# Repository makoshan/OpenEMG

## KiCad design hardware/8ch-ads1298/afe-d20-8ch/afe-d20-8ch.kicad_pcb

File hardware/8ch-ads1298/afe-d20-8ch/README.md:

# C08B 纯单面 8 通道采集板 · 圆孔版 D20-8CH（2026-11-12）

基于 C08B 正面基准布局 人工正面布局与已修清全部安全/电气缺陷的 `../../16ch-c08b-round/afe-d20/afe-d20-silk.kicad_pcb`（`31323826…`）派生，同步吸收 `ProPrj_ads1298v3.4` 单颗 ADS1298 八路拓扑：

- **纯正面单面贴**：保留正面全部 76 颗贴片器件（`V4_U1` ADS1298 CH1–8、`V4_FPC1` 34P、`J_AFE` 20P、`V4_LM27762` ±2.5V、`V4_X1` 2.048 MHz、`D910–D927` ESD401、`V4_U3–U6` 15k 排阻、`V4_C72–C79` 22 pF 差分电容、`V4_R18` 0R 单点接地、`V4_R34` 392 kΩ RLD 限流）+ `TP901/TP902` + `H901–H904`；删除背面全部 53 个封装（51 颗贴片 + `TP903/TP904`）。
- **背面整面绿油绝缘**：`B.Paste = 0`、`B.Mask = 0`，背面无裸露焊盘或凸起阻容，可直接贴合 `302025` 锂电池；省去双面贴片换面费。
- **主控与外壳 1:1 兼容**：板框 `43.10 × 36.50 mm` 与 `D20` 完全一致，`J_AFE`（20P）与主控板 `R4U6` 逐脚对插（3/4 脚 `ADS_DRDY_B`/`ADS_CS_B` 置为 `NC`）。
- **走线与 DRC**：仅对原借道背面焊盘连通正面的 7 条网络补齐纳米级 135°/共线桥接，剪除 140 段残桩与 10 颗单端过孔，倒角 `V4_REF2` 原三岔口留下的 1 处 90° 拐角。KiCad 10 DRC（含重铺）0 违规 / 0 未连，`route_lint` 七项硬指标全 0，`smt_dfm_gate` 通过。

## 图纸、逐针核对表与嘉立创工程（对标 16 通道 v0.01 交付标准）

| 文件 / 目录 | 说明 |
|---|---|
| [`PINOUT-AND-REVIEW.md`](PINOUT-AND-REVIEW.md) · [`pinout-34p-20p.csv`](pinout-34p-20p.csv) | **34P 表带接口（`V4_FPC1`）与 20P 板间接口（`J_AFE` `k ↔ 21−k`）逐针核对总表**、固件寄存器表、制造包 SHA-256 绑定与五阶段验收记录表 |
| [`views/schematic.pdf`](views/schematic.pdf) | **11 页全套矢量可搜索原理图 PDF**（P1 整机框图、P2 电源树、P3–P7 主控板 `R4U6`、P8–P11 采集板 `D20-8CH`） |
| [`views/afe-schematic.pdf`](views/afe-schematic.pdf) | **6 页采集板独立矢量可搜索原理图 PDF**（P1 整机框图、P2 电源树、P3–P6 采集板详图；同步更新 [`schematics-8ch/C08B-8ch采集板原理图-D20-8CH-20261113.pdf`](schematics-8ch/C08B-8ch采集板原理图-D20-8CH-20261113.pdf)） |
| [`views/d20-8ch-wiring-orientation.svg`](views/d20-8ch-wiring-orientation.svg) · [`.png`](views/d20-8ch-wiring-orientation.png) | **贴肤侧 18 枚电极编号（盒底 6 + 北短带 4 + 南长带 8）与 34P/20P 座子开口朝向核对图** |
| [`views/d20-8ch-system-zh.svg`](views/d20-8ch-system-zh.svg) · [`-en.svg`](views/d20-8ch-system-en.svg) | P1 整机框图（中英双语矢量图） |
| [`views/d20-8ch-power-zh.svg`](views/d20-8ch-power-zh.svg) · [`-en.svg`](views/d20-8ch-power-en.svg) | P2 电源树与实测记录栏（中英双语矢量图） |
| [`views/afe-copper.png`](views/afe-copper.png) · [`views/schematic-afe-input-preview.png`](views/schematic-afe-input-preview.png) | 4 层铜皮预览与 34P 电极输入保护页预览 |
| [`jlc-eda/C08B-8ch全套汇总-主控R4U6-采集D20-8CH单面.epro2`](jlc-eda/C08B-8ch全套汇总-主控R4U6-采集D20-8CH单面.epro2) | 嘉立创 EDA 专业版全套双板工程（含 **11 页原理图**：`01.01 整机框图`、`01.02 电源树`、主控 5 页、采集 4 页） |
| [`jlc-eda/C08B-AFE采集板-D20-8CH-单面8路-原理图+PCB+3D.epro2`](jlc-eda/C08B-AFE采集板-D20-8CH-单面8路-原理图+PCB+3D.epro2) | 嘉立创 EDA 专业版采集板独立工程（含 **6 页原理图**：`01.01 整机框图`、`01.02 电源树`、采集 4 页） |

状态：**待人工工程师独立审板**（自动化逐脚对板与 DRC 已过；未人工审板、未打样、未上台架、未过人体安全门）。

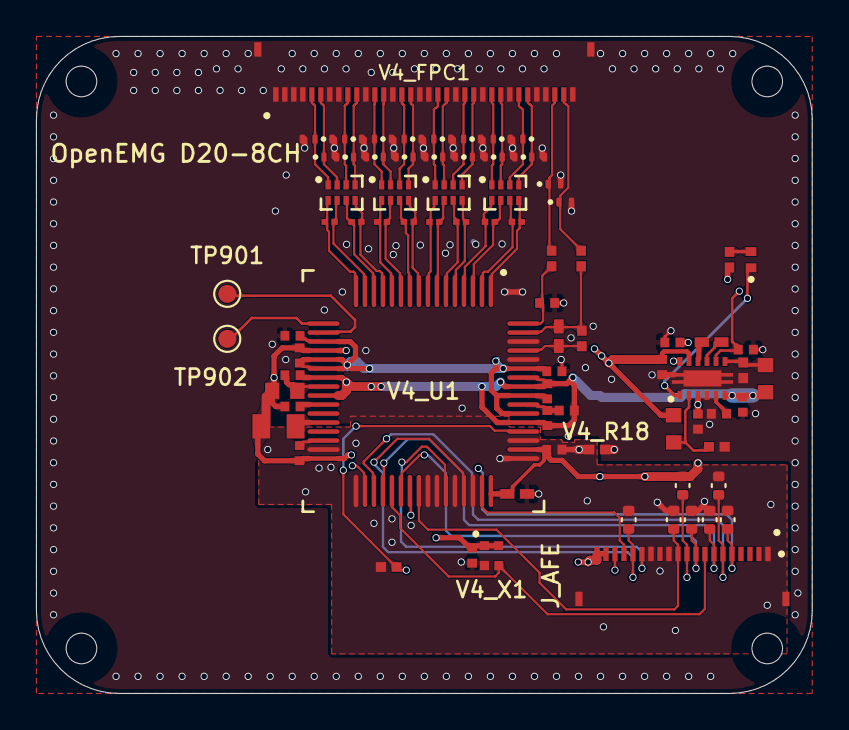
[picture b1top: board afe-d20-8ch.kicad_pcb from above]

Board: 4 copper layers, 43.1 x 36.5 mm, 82 parts (0 on the bottom side), 67 nets.

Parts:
C901: 10uF; C901
C902: 4.7uF; C902
D901: XL-1005UGC; D901
D910: ESD401DPYR; D910
D911: ESD401DPYR; D911
D912: ESD401DPYR; D912
D913: ESD401DPYR; D913
D914: ESD401DPYR; D914
D915: ESD401DPYR; D915
D916: ESD401DPYR; D916
D917: ESD401DPYR; D917
D918: ESD401DPYR; D918
D919: ESD401DPYR; D919
D920: ESD401DPYR; D920
D921: ESD401DPYR; D921
D922: ESD401DPYR; D922
D923: ESD401DPYR; D923
D924: ESD401DPYR; D924
D925: ESD401DPYR; D925
D926: ESD401DPYR; D926
D927: ESD401DPYR; D927
H901: M1.4 NPTH 1.7; H901
H902: M1.4 NPTH 1.7; H902
H903: M1.4 NPTH 1.7; H903
H904: M1.4 NPTH 1.7; H904
J_AFE: FH34SRJ-20S-0.5SH(50) (LCSC C2802370); Hirose_FH34SRJ-20S-0.5SH
R801: 10k; R801
R803: 10k; R803
R804: 10k; R804
R805: 10k; R805
R806: 10k; R806
R807: 10k; R807
R808: 10k; R808
R901: 10kΩ; R901
TP901: V4_REF2; TP901
TP902: V4_REF1; TP902
V4_C31: 1uF; V4_C31
V4_C32: 100nF; V4_C32
V4_C33: 1uF; V4_C33
V4_C34: 100nF; V4_C34
V4_C35: 1uF; V4_C35
V4_C36: 100nF; V4_C36
V4_C37: 100nF; V4_C37
V4_C43: 1uF; V4_C43
V4_C44: 1uF; V4_C44
V4_C45: 100nF; V4_C45
V4_C46: 10uF; V4_C46
V4_C47: 10nF; V4_C47
V4_C48: 100nF; V4_C48
V4_C49: 1uF; V4_C49
V4_C50: 100nF; V4_C50
V4_C54: 22uF; V4_C54
V4_C72: 22pF; V4_C72
V4_C73: 22pF; V4_C73
V4_C74: 22pF; V4_C74
V4_C75: 22pF; V4_C75
V4_C76: 22pF; V4_C76
V4_C77: 22pF; V4_C77
V4_C78: 22pF; V4_C78
V4_C79: 22pF; V4_C79
V4_C81: 100nF; V4_C81
V4_C82: 100nF; V4_C82
V4_C83: 2.2uF; V4_C83
V4_C84: 2.2uF; V4_C84
V4_C123: 100pF; V4_C123
V4_FPC1: FH34SRJ-34S-0.5SH(50) (LCSC C424660); Hirose_FH34SRJ-34S-0.5SH
V4_LM27762: LM27762DSSR; V4_LM27762
V4_R17: 10K; V4_R17
V4_R18: 0R; V4_R18
V4_R24: 392K; V4_R24
V4_R26: 107k; V4_R26
V4_R27: 100kΩ; V4_R27
V4_R28: 100kΩ; V4_R28
V4_R29: 104k; V4_R29
V4_R34: 392K; V4_R34
V4_R35: 10K; V4_R35
V4_U1: ADS1298IPAGR; V4_U1
V4_U3: 15kΩ; V4_U3
V4_U4: 15kΩ; V4_U4
V4_U5: 15kΩ; V4_U5
V4_U6: 15kΩ; V4_U6
V4_X1: 2.048MHz; V4_X1

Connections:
3V3: C901.2, J_AFE.19, J_AFE.20, R801.2, R901.1, V4_C31.2, V4_C32.2, V4_C37.2, V4_C81.2, V4_C82.2, V4_LM27762.3, V4_LM27762.8, V4_LM27762.12, V4_U1.48, V4_U1.50, V4_X1.1, V4_X1.4
ADS_CLKSEL: J_AFE.18, V4_R17.2, V4_U1.52
ADS_CS_A: J_AFE.10, R801.1, V4_U1.39
ADS_DRDY_A: J_AFE.17, V4_U1.47
ADS_PWDN: J_AFE.6, R804.1, V4_U1.35
ADS_RESET: J_AFE.7, R803.1, V4_U1.36
ADS_START: J_AFE.9, R805.1, V4_U1.38
AFE_CLK_IN: J_AFE.8, V4_U1.37, V4_X1.3
AFE_GPIO3: J_AFE.16, R808.1, V4_U1.45
AGND: C901.1, C902.1, D910.2, D911.2, D912.2, D913.2, D914.2, D915.2, D916.2, D917.2, D918.2, D919.2, D920.2, D921.2, D922.2, D923.2, D924.2, D925.2, D926.2, D927.2, V4_C33.1, V4_C34.1, V4_C81.1, V4_C82.1, V4_C83.1, V4_C84.1, V4_C123.2, V4_FPC1.1, V4_FPC1.2, V4_FPC1.3, V4_FPC1.4, V4_FPC1.7, V4_FPC1.8, V4_FPC1.11, V4_FPC1.14, V4_FPC1.17, V4_FPC1.18, V4_FPC1.21, V4_FPC1.24, V4_FPC1.27, V4_FPC1.30, V4_FPC1.31, V4_FPC1.34, V4_FPC1.MP, V4_LM27762.4, V4_LM27762.13, V4_R18.2, V4_R27.1, V4_R28.2, V4_U1.60, V4_U1.62
DIN_B: J_AFE.5, R807.1, V4_U1.34
DOUT_B: J_AFE.15, V4_U1.43
GND: J_AFE.1, J_AFE.12, J_AFE.14, J_AFE.21, J_AFE.22, R803.2, R804.2, R805.2, R806.2, R807.2, R808.2, V4_C31.1, V4_C32.1, V4_C37.1, V4_R17.1, V4_R18.1, V4_U1.31, V4_U1.33, V4_U1.41, V4_U1.42, V4_U1.44, V4_U1.46, V4_U1.49, V4_U1.51, V4_X1.2
SCLK_B: J_AFE.11, R806.1, V4_U1.40
V4_$1N19: V4_C45.2, V4_C46.1, V4_U1.24
V4_$1N24: V4_C44.2, V4_U1.26
V4_$1N25: V4_C54.2, V4_U1.28
V4_$1N26: V4_C43.2, V4_U1.30
V4_$1N44: V4_C48.2, V4_C49.1, V4_U1.55
V4_$1N350: V4_C123.1, V4_R35.1, V4_U1.64
V4_$2N83: D927.1, V4_FPC1.5, V4_U6.1
V4_$2N85: D926.1, V4_FPC1.6, V4_U6.2
V4_$2N86: D925.1, V4_FPC1.9, V4_U6.3
V4_$2N87: D924.1, V4_FPC1.10, V4_U6.4
V4_$2N90: D921.1, V4_FPC1.15, V4_U5.3
V4_$2N93: D918.1, V4_FPC1.20, V4_U4.2
V4_$2N94: D917.1, V4_FPC1.22, V4_U4.3
V4_$2N95: D916.1, V4_FPC1.23, V4_U4.4
V4_$2N96: D915.1, V4_FPC1.25, V4_U3.1
V4_$2N97: D914.1, V4_FPC1.26, V4_U3.2
V4_$2N98: D913.1, V4_FPC1.28, V4_U3.3
V4_$2N111: D919.1, V4_FPC1.19, V4_U4.1
V4_$2N118: D923.1, V4_FPC1.12, V4_U5.1
V4_$2N119: D922.1, V4_FPC1.13, V4_U5.2
V4_$2N120: D920.1, V4_FPC1.16, V4_U5.4
V4_$2N121: D912.1, V4_FPC1.29, V4_U3.4
V4_$3N49: D901.2, R901.2
V4_$3N56: V4_LM27762.2, V4_R26.1, V4_R27.2
V4_$3N57: V4_C50.1, V4_LM27762.9
V4_$3N58: V4_C50.2, V4_LM27762.10
V4_$3N60: V4_LM27762.7, V4_R28.1, V4_R29.2
V4_$3N62: C902.2, V4_LM27762.5
V4_+2.5V: V4_C33.2, V4_C34.2, V4_C35.2, V4_C36.2, V4_C83.2, V4_LM27762.11, V4_R26.2, V4_U1.19, V4_U1.21, V4_U1.22, V4_U1.54, V4_U1.56, V4_U1.59
V4_-2.5V: V4_C35.1, V4_C36.1, V4_C43.1, V4_C44.1, V4_C45.1, V4_C46.2, V4_C48.1, V4_C49.2, V4_C54.1, V4_C84.2, V4_LM27762.6, V4_R29.1, V4_U1.20, V4_U1.23, V4_U1.25, V4_U1.32, V4_U1.53, V4_U1.57, V4_U1.58
V4_BIASINV1: V4_C47.1, V4_R24.1, V4_U1.61
V4_BIASOUT1: V4_C47.2, V4_R24.2, V4_R34.1, V4_U1.63
V4_BIAS_DRV1: D910.1, V4_FPC1.33, V4_R34.2
V4_IN1N: V4_C72.1, V4_U1.15, V4_U6.7
V4_IN1P: V4_C72.2, V4_U1.16, V4_U6.8
V4_IN2N: V4_C73.1, V4_U1.13, V4_U6.5
V4_IN2P: V4_C73.2, V4_U1.14, V4_U6.6
V4_IN3N: V4_C74.1, V4_U1.11, V4_U5.7
V4_IN3P: V4_C74.2, V4_U1.12, V4_U5.8
V4_IN4N: V4_C75.1, V4_U1.9, V4_U5.5
V4_IN4P: V4_C75.2, V4_U1.10, V4_U5.6
V4_IN5N: V4_C76.1, V4_U1.7, V4_U4.7
V4_IN5P: V4_C76.2, V4_U1.8, V4_U4.8
V4_IN6N: V4_C77.1, V4_U1.5, V4_U4.5
V4_IN6P: V4_C77.2, V4_U1.6, V4_U4.6
V4_IN7N: V4_C78.1, V4_U1.3, V4_U3.7
V4_IN7P: V4_C78.2, V4_U1.4, V4_U3.8
V4_IN8N: V4_C79.1, V4_U1.1, V4_U3.5
V4_IN8P: V4_C79.2, V4_U1.2, V4_U3.6
V4_POWERGOOD: D901.1, V4_LM27762.1
V4_REF1: TP902.1, V4_U1.17
V4_REF2: TP901.1, V4_U1.18
V4_WCT: D911.1, V4_FPC1.32, V4_R35.2

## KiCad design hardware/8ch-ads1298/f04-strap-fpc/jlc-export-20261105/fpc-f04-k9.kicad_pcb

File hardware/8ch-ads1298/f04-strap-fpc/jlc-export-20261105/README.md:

# F04 八通道软板导入嘉立创EDA（2026-11-05）

状态：已实现未验收。交付文件 `exports/嘉立创-F04-八通道软板-20261105/F04-八通道软板-原理图+PCB.epro2`，含原理图和 PCB。下单仍以 `v12/strap-f04-order/F04-FPC-样品打样5片.zip` 为准；软板源文件和订单未改。

## 重出步骤

官方 CLI 要在 Bash 沙箱外跑（沙箱里 `open` 不返回）。全程用无头会话，不碰别的窗口。

1. `python3 tools/kicad10_to_9_nets.py ../fpc-f04.kicad_pcb fpc-f04-k9.kicad_pcb`：KiCad 10 写法导入会丢铜线。
2. `python3 k9_no_tail_paste.py fpc-f04-k9.kicad_pcb`：尾端 17 个手焊盘本来没有 F.Paste，嘉立创导入后会自动开钢网，这里加负余量关掉。
3. K9 板连同 `.kicad_pro`、`.kicad_sch`、`FPC.kicad_sym`、两个 lib-table、`FPC.pretty/` 压成 zip，板文件名用 `fpc-f04.kicad_pcb`。
4. easyeda-eprj3 的 `init.js` 建空工程，`python3 import_f04.py <工程.eprj3> <zip>` 导入并配板。
5. `../../c08-eprj3-20261102/sync_uid.py <工程文件夹>` 配对元件编号，`python3 apply_rules_f04.py <工程.eprj3>` 写规则（铜间距 0.10、线宽 ≥ 0.15、铜到板边 0.30）。
6. `../../c08-eprj3-20261102/export_epro2.py <工程.eprj3> <输出.epro2>`。

## 验证（量导出的文件，不只量源工程）

| 项 | 结果 | 证据 |
|---|---|---|
| 器件 / 走线 / 飞线 | 18 = 18，799 = 799，飞线 0 | `verify-source.json`、`reimport-check.json` |
| 焊盘网络 | 34 个逻辑脚 0 不符；17 网长度差 0 | `verify-source.json` |
| 嘉立创解析的原理图网表对 PCB | 34 脚 0 不符 | `native-check.json` |
| 导回后 DRC | 只剩 Netlist Error 1 条 | `reimport-check.json` |
| DRC 阳性对照 | 注入异网短线报 2 条线距、1 条焊盘距、2 条连接错误，删除后恢复 | `reimport-check.json` |
| 铜 / 覆盖膜开窗 / 钢网 Gerber 对下单包 | 异或面积 0.0006 / 0 / 0 mm² | `gerber-diff.json` |
| Gerber 比对阳性对照 | 修钢网前报差异 30.6 mm²，正好是 17 × 3.0 × 0.6 | 本轮输出 |

## 已知差异

- **Netlist Error 1 条**：原理图和 PCB 的器件属性不同（`Name`、`Channel ID`、引脚名等），网络一致。改 PCB 的 `Name` 后这条仍在，没再追。
- **丝印字更小**：26 个字内容和中心位置都对，嘉立创字体比 KiCad 小约四成。
- **板框线宽**：中心线都是 186.8×23 mm；嘉立创线宽 0.15，下单包 0.05。
- **未比对**：PI 补强只作为自定义层上的矩形框导入。叠层没写成 106 µm 软板，在嘉立创里一键下单不能代替 `FAB-SPEC.md`。

`fpc-f04-k9.kicad_pcb` 是中间板，不入库，也不要拿回 KiCad 改。

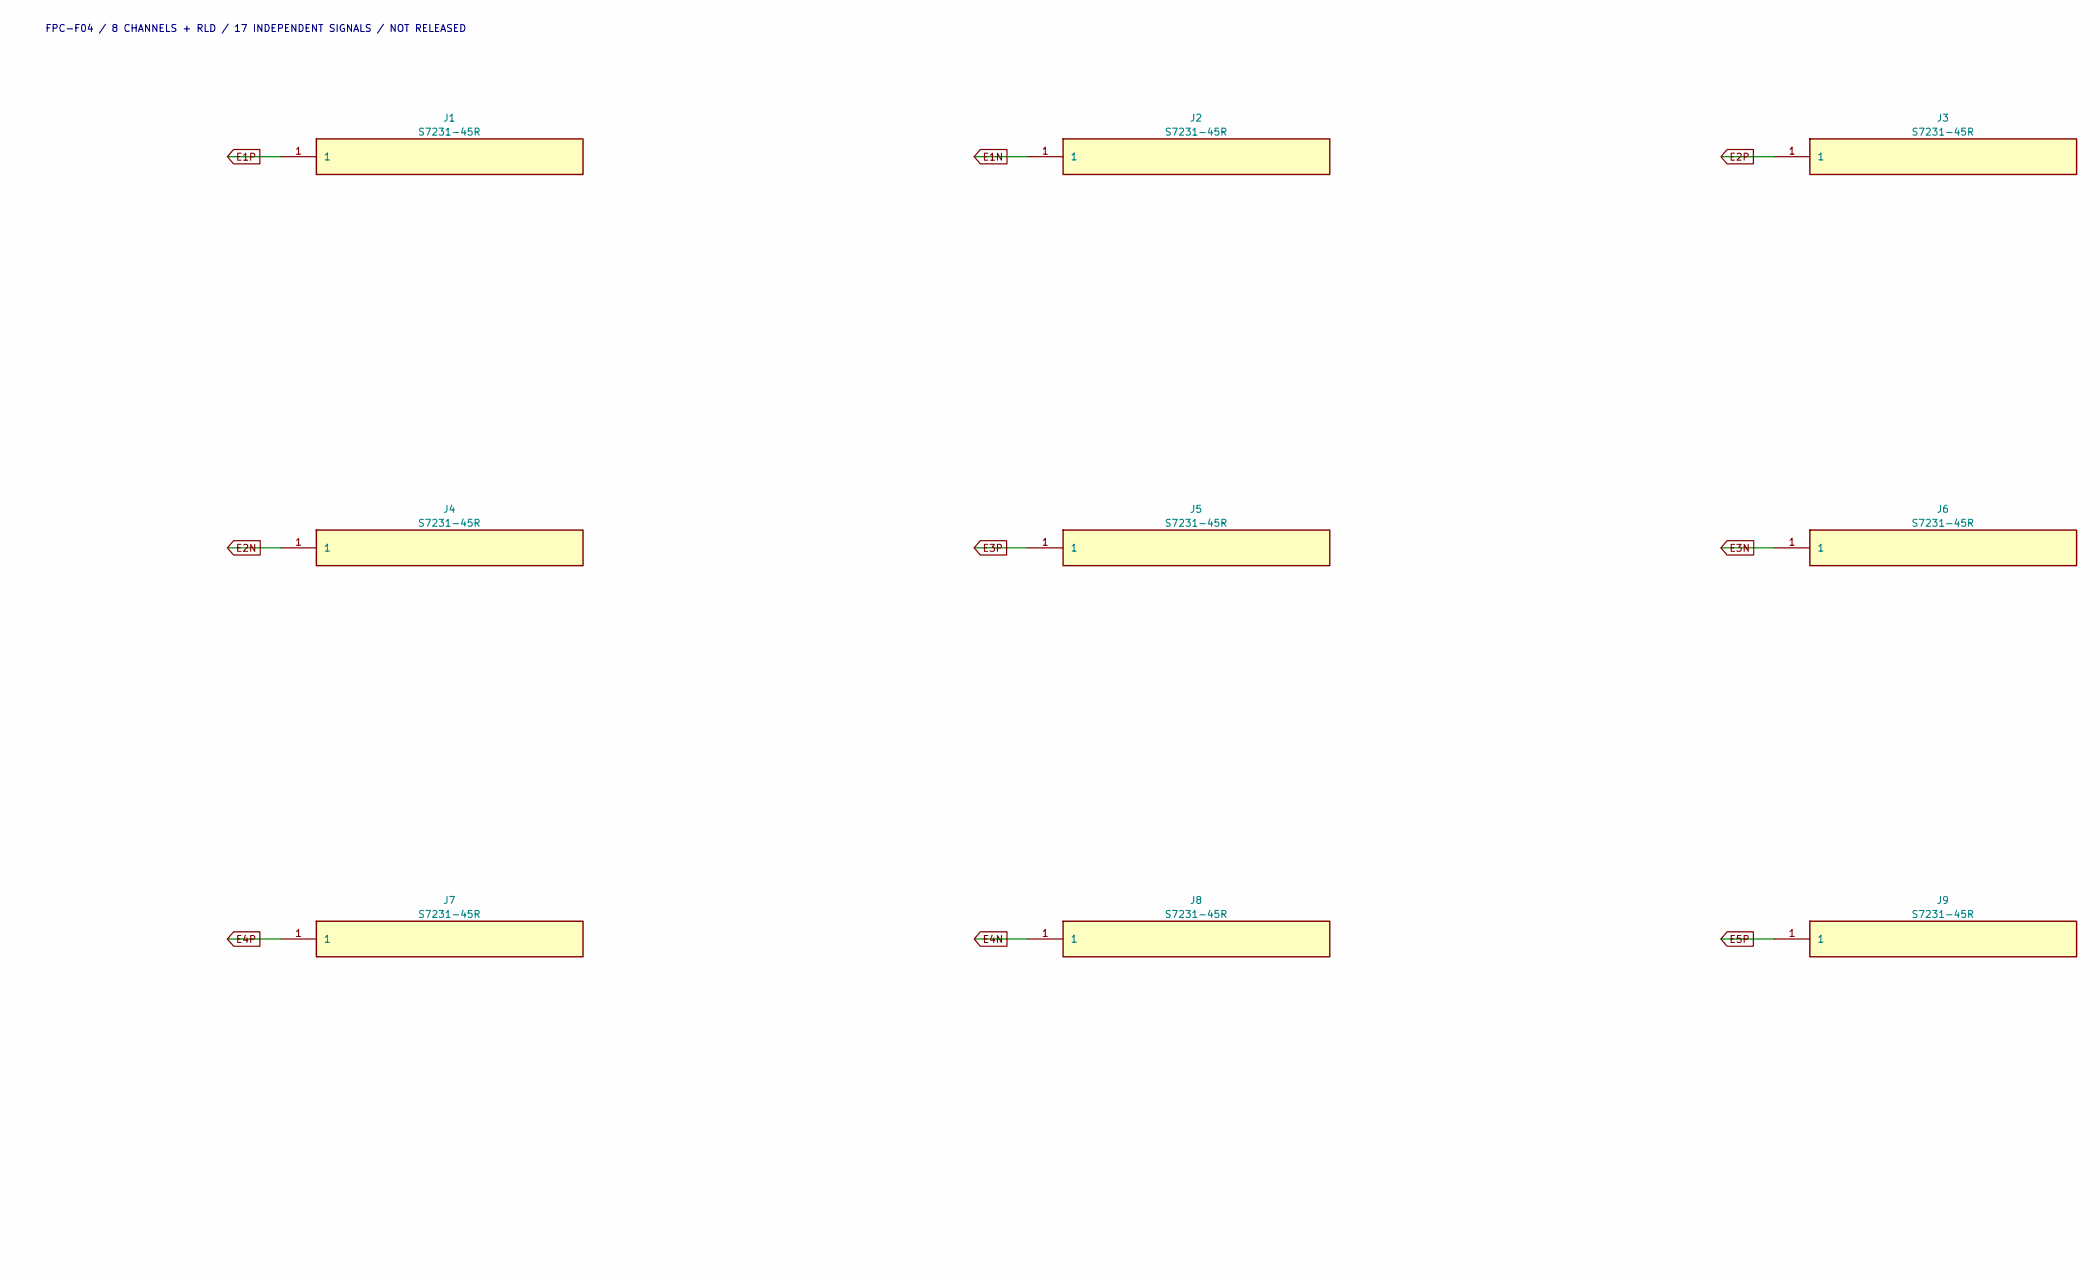
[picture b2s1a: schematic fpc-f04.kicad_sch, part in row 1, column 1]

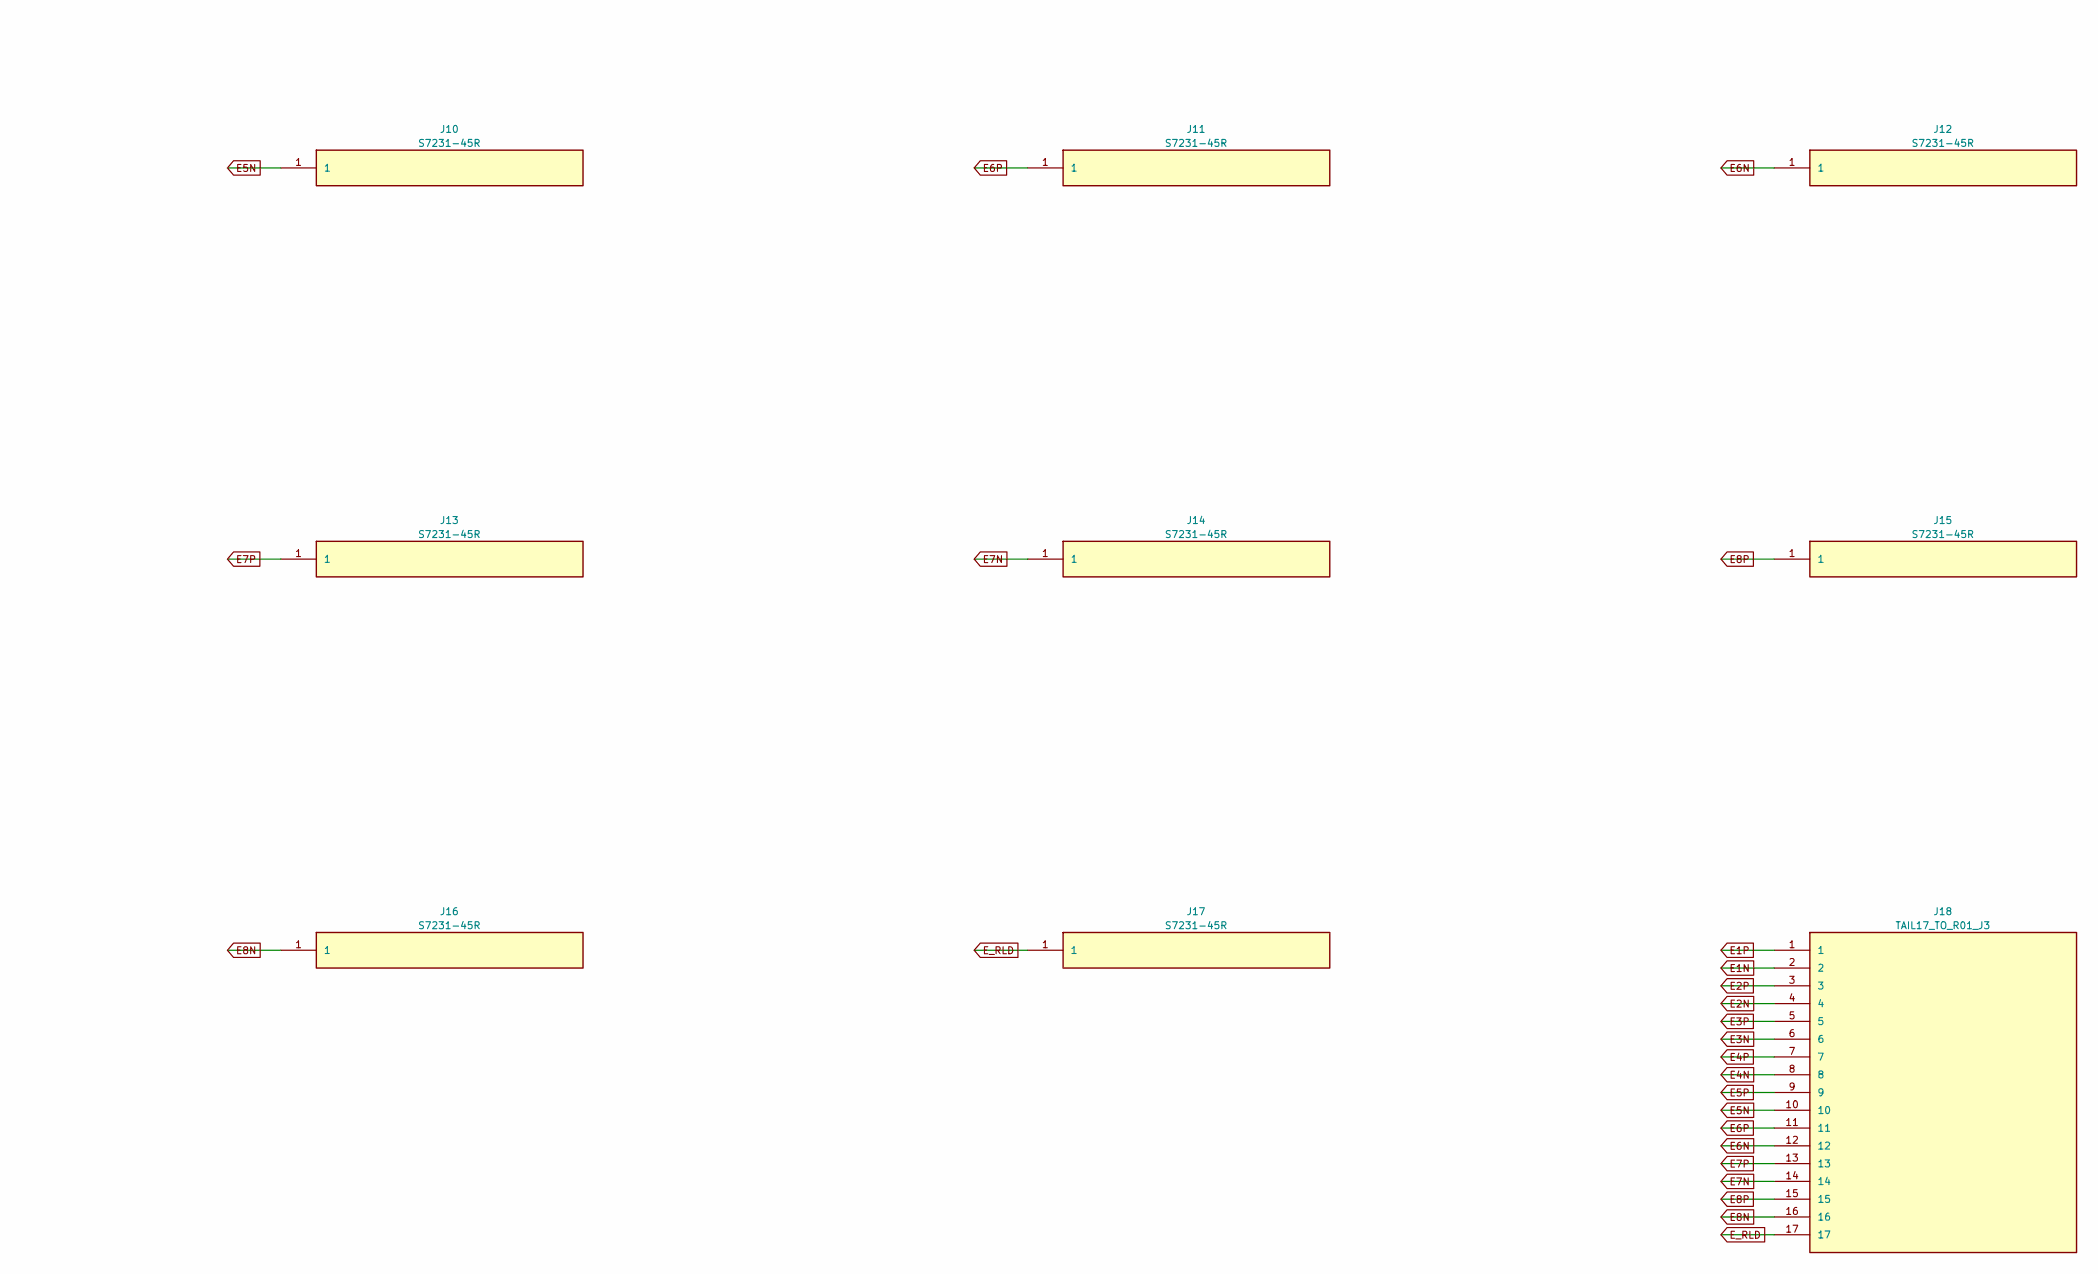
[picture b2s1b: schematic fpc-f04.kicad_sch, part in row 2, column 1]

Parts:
J1, J2, J3, J4, J5, J6, J7, J8, J9, J10, J11, J12, J13, J14, J15, J16, J17: S7231-45R; S7231
J18: TAIL17_TO_R01_J3; TAIL17

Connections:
E1N: J2.1, J18.2
E1P: J1.1, J18.1
E2N: J4.1, J18.4
E2P: J3.1, J18.3
E3N: J6.1, J18.6
E3P: J5.1, J18.5
E4N: J8.1, J18.8
E4P: J7.1, J18.7
E5N: J10.1, J18.10
E5P: J9.1, J18.9
E6N: J12.1, J18.12
E6P: J11.1, J18.11
E7N: J14.1, J18.14
E7P: J13.1, J18.13
E8N: J16.1, J18.16
E8P: J15.1, J18.15
E_RLD: J17.1, J18.17

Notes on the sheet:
FPC-F04 / 8 CHANNELS + RLD / 17 INDEPENDENT SIGNALS / NOT RELEASED

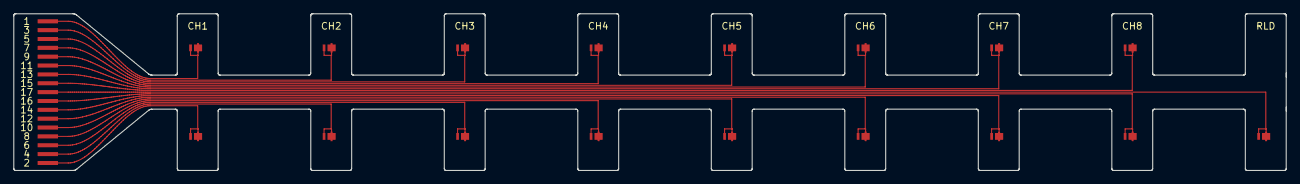
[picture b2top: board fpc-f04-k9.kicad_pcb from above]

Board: 2 copper layers, 186.8 x 23.0 mm, 18 parts (0 on the bottom side), 17 nets.

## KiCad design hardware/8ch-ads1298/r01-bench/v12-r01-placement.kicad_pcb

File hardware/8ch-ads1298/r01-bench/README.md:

# V12 R01：离体台架候选

**后续实板测试（2026-10-24）**　R01 在短接输入模式完成一次 10 分钟采集。上位机归档包含 91,368 个包、1,187,774 帧；重读归档后，帧序号连续，停止时的计数吻合。这次测试覆盖离体台架的数据传输。下面的设计交付记录保留了打样前的状态。

8通道ADS1298 + 外接XIAO nRF52840 Sense；65×60×1.6mm四层。原V12和F04保留。本版没有缩进佩戴主舱，也未放行人体连接或下单。

| 面板 | 当前内容 | 验收边界 |
|---|---|---|
| A 电路 | 208件，548个连接脚，原生KiCad 12页、S/Q与分组BOM | ERC与网表只证明文件一致；供电瞬态须实测 |
| B 封装 | 真实脚号、极性、Samtec/JST/Molex接口、自定义TI小封装 | 孔公差、器件批次、有效电容及实际压接未验 |
| C PCB | 8对输入按ADC针序，关键模拟/开关/去耦预先布线，内层1为地 | 最终检查见board-check.json；DRC不代替模拟性能 |
| D 固件 | F05真实ADS路径，19项主机正反例；2k/4k镜像互核 | 默认锁定、未刷机；IMU同步未实现 |
| E 文件包 | 导出脚本要求新跑原生DRC，并在解压后重跑 | 只有package-check.json成功记录才算导出完成 |
| F 实物 | [接口表](INTERFACES.md)、[离体验收表](BENCH-ACCEPTANCE.md) | XIAO/电池/线束、波形、噪声、无线和整圈装配仍开放 |

本地已实跑：208封装、1539段铜线、253过孔；原生DRC/未连/原理图一致性均零，577个实际焊盘逐一核网，过孔侵入SMD为零。

本地完成判据：`check_candidate.py`通过且6项负控拒绝；新跑原生ERC与PCB DRC/原理图一致性均零；`check_board.py`读取真实焊盘与铜通过；导出后解压重验通过。独立复核不得由这些数字替代。

复现顺序：`build_candidate.py` → `build_footprints.py` → `build_schematic.py` → `build_board.py` → `lock_references.py --placement` → 用现有Freerouting对DSN补线 → `finish_board.py` → 必要时`close_remaining.py`逐条补连 → `sync_board_metadata.py` → `check_board.py` → `export_review.py`。原生Python和CLI路径在脚本中显式记录；关键线随DSN保留fix/protect约束，补线不能擅自改动。生成器是初始布局入口；本版最终位置与手工出口调整以保存的原生PCB为准，重新生成不能覆盖已验收候选。

`V12-R01-REVIEW.zip`是可检查的完整候选，`V12-R01-GERBER-REVIEW-NOT-RELEASED.zip`只含制板层/钻孔。名称中的REVIEW表示尚有实物与工艺门；不要直接把候选当已放行制造版本。

审查证据在仓库`evidence/2026-10-04-v12-manufacturing-r01/`。此前失败路由、EP边缘相切负例及独立复核意见保留。原始资料和大构建产物仅本地保存，哈希随源码记录。

采购分组BOM含198件实体器件（195件SMD＋3件THT连接器）；10个裸铜测试点不采购。贴装坐标表仅含195件SMD，THT须单独安排插装；封装图形放在装配层，不能把装配层当丝印下单。

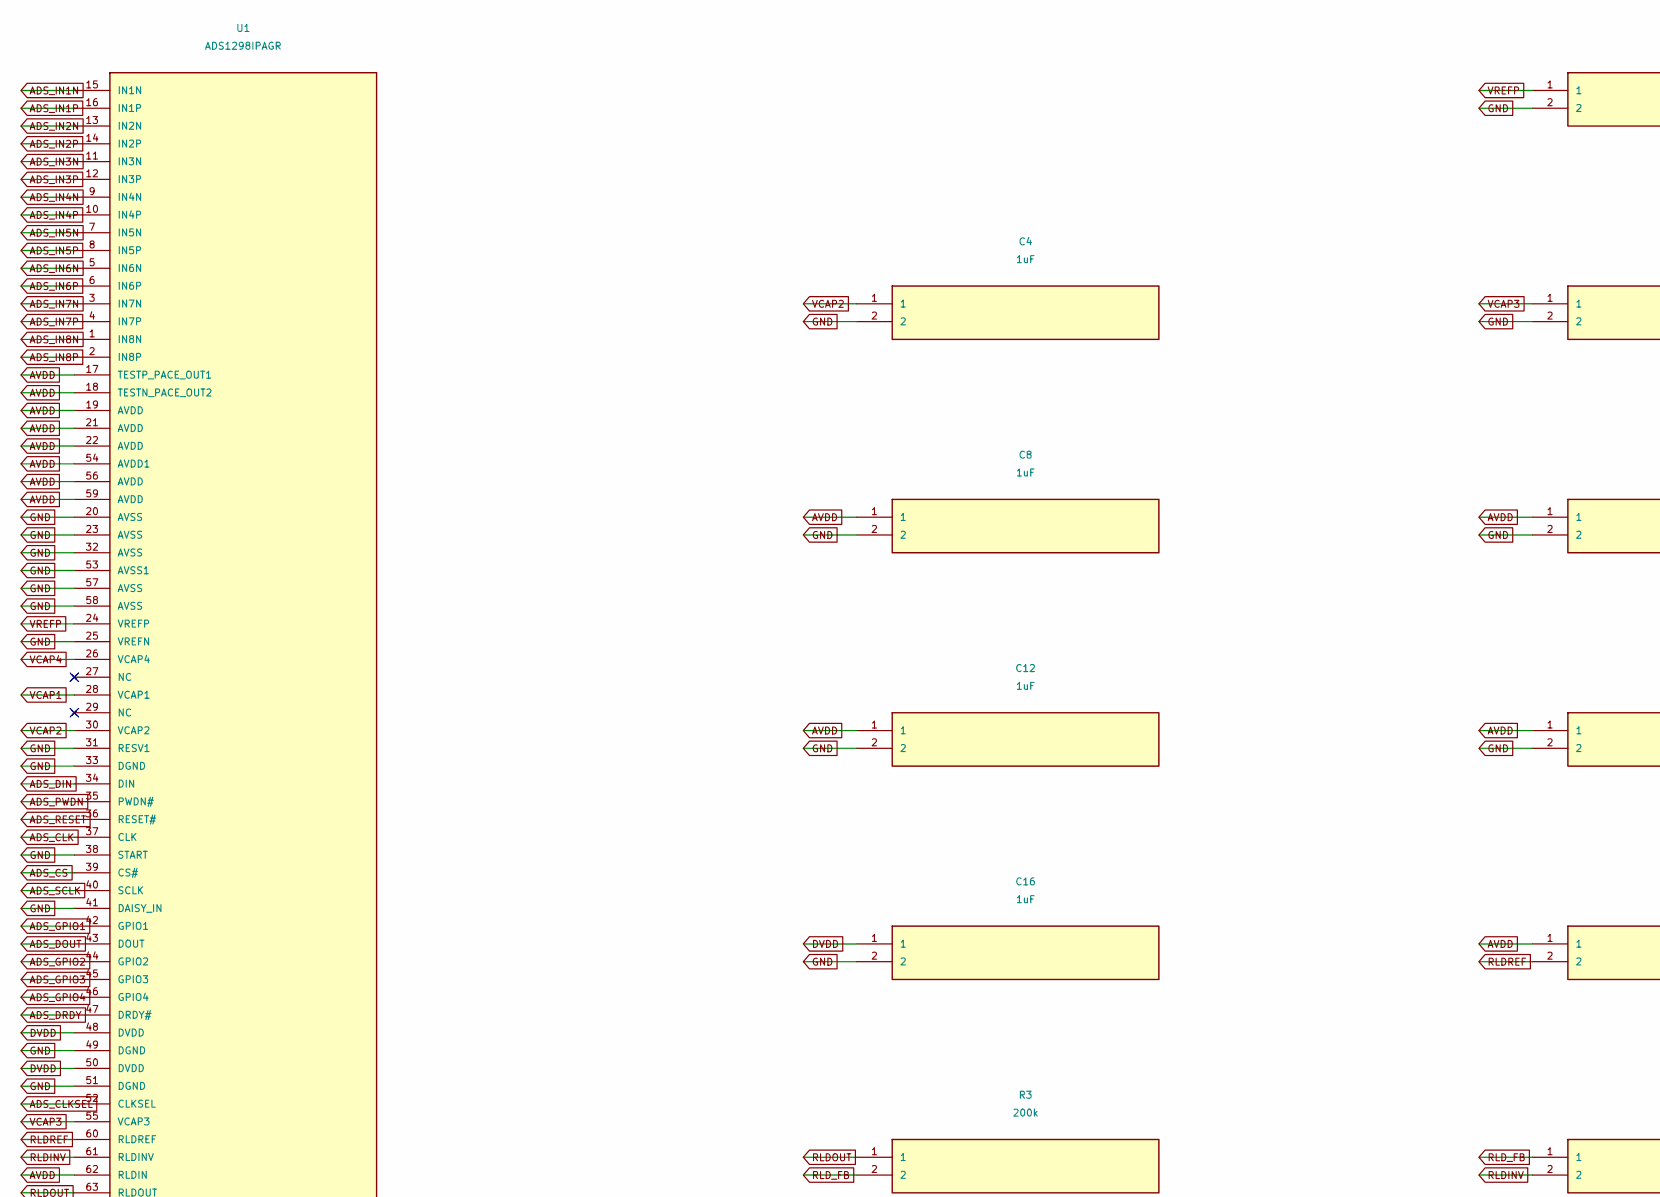
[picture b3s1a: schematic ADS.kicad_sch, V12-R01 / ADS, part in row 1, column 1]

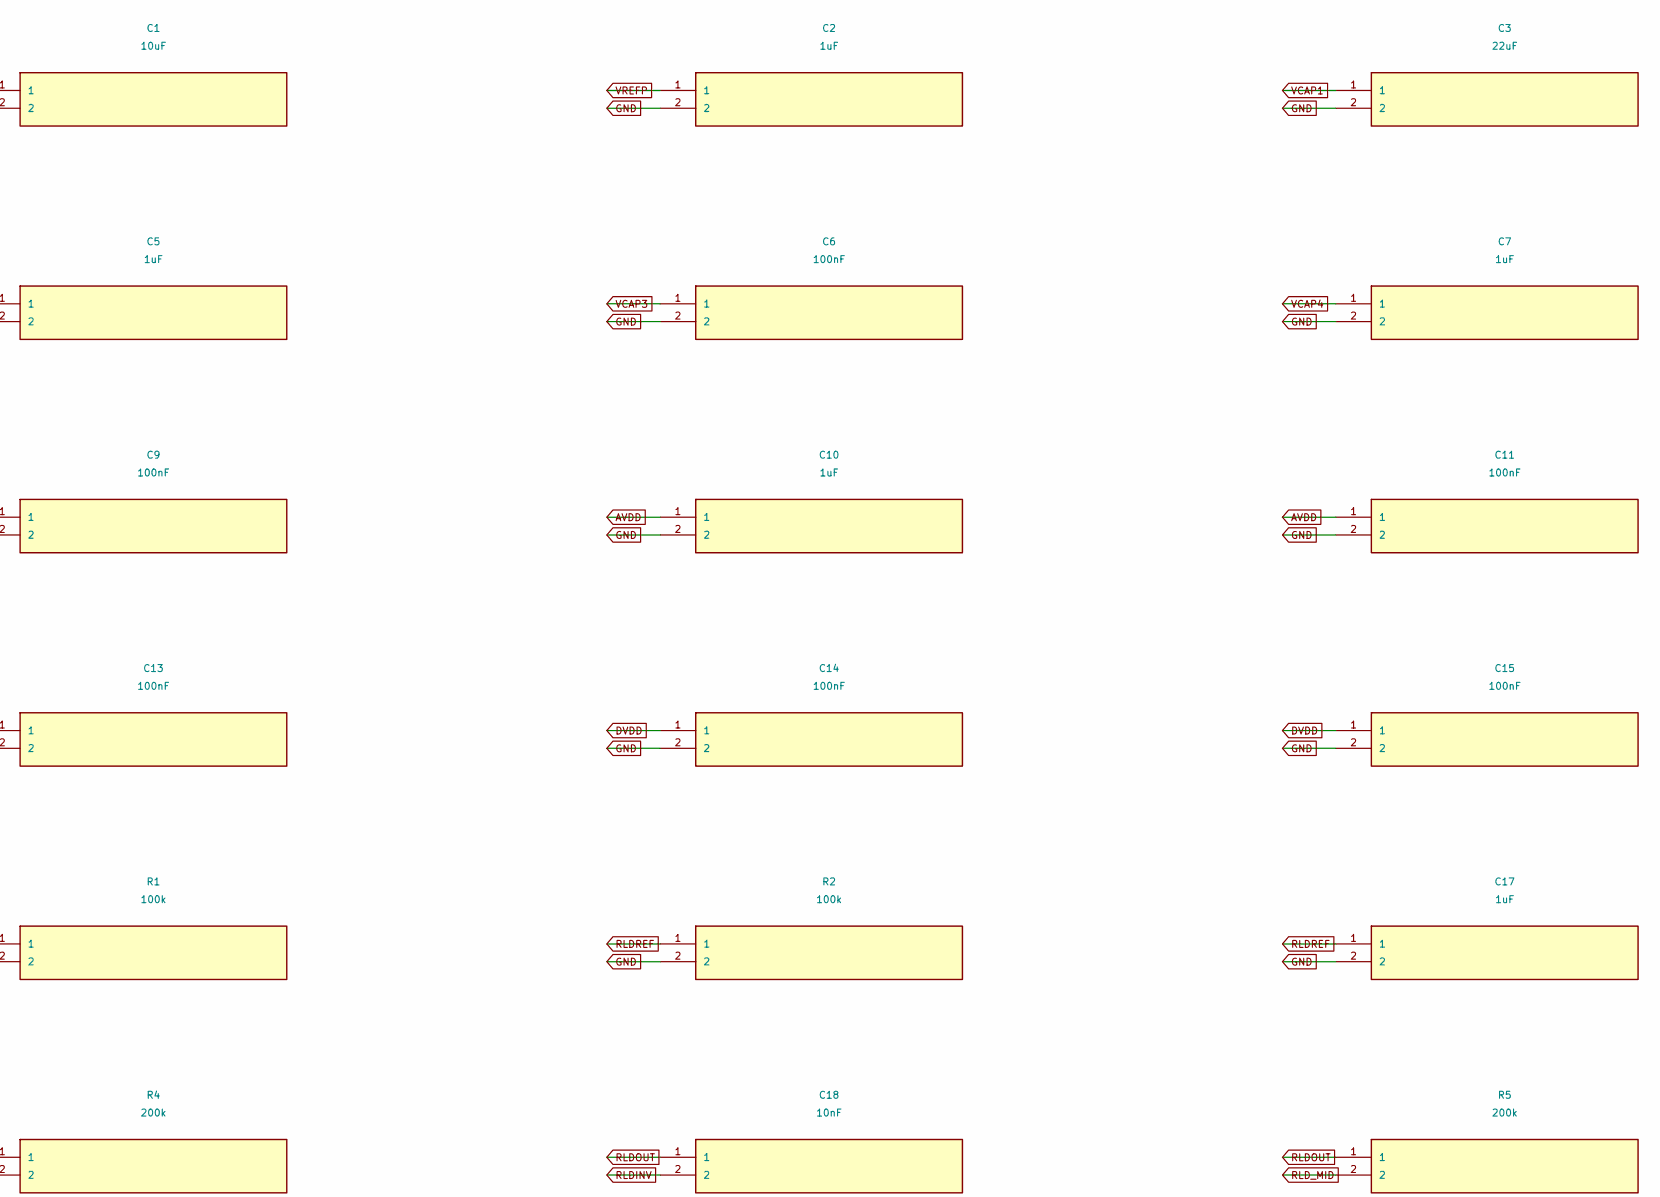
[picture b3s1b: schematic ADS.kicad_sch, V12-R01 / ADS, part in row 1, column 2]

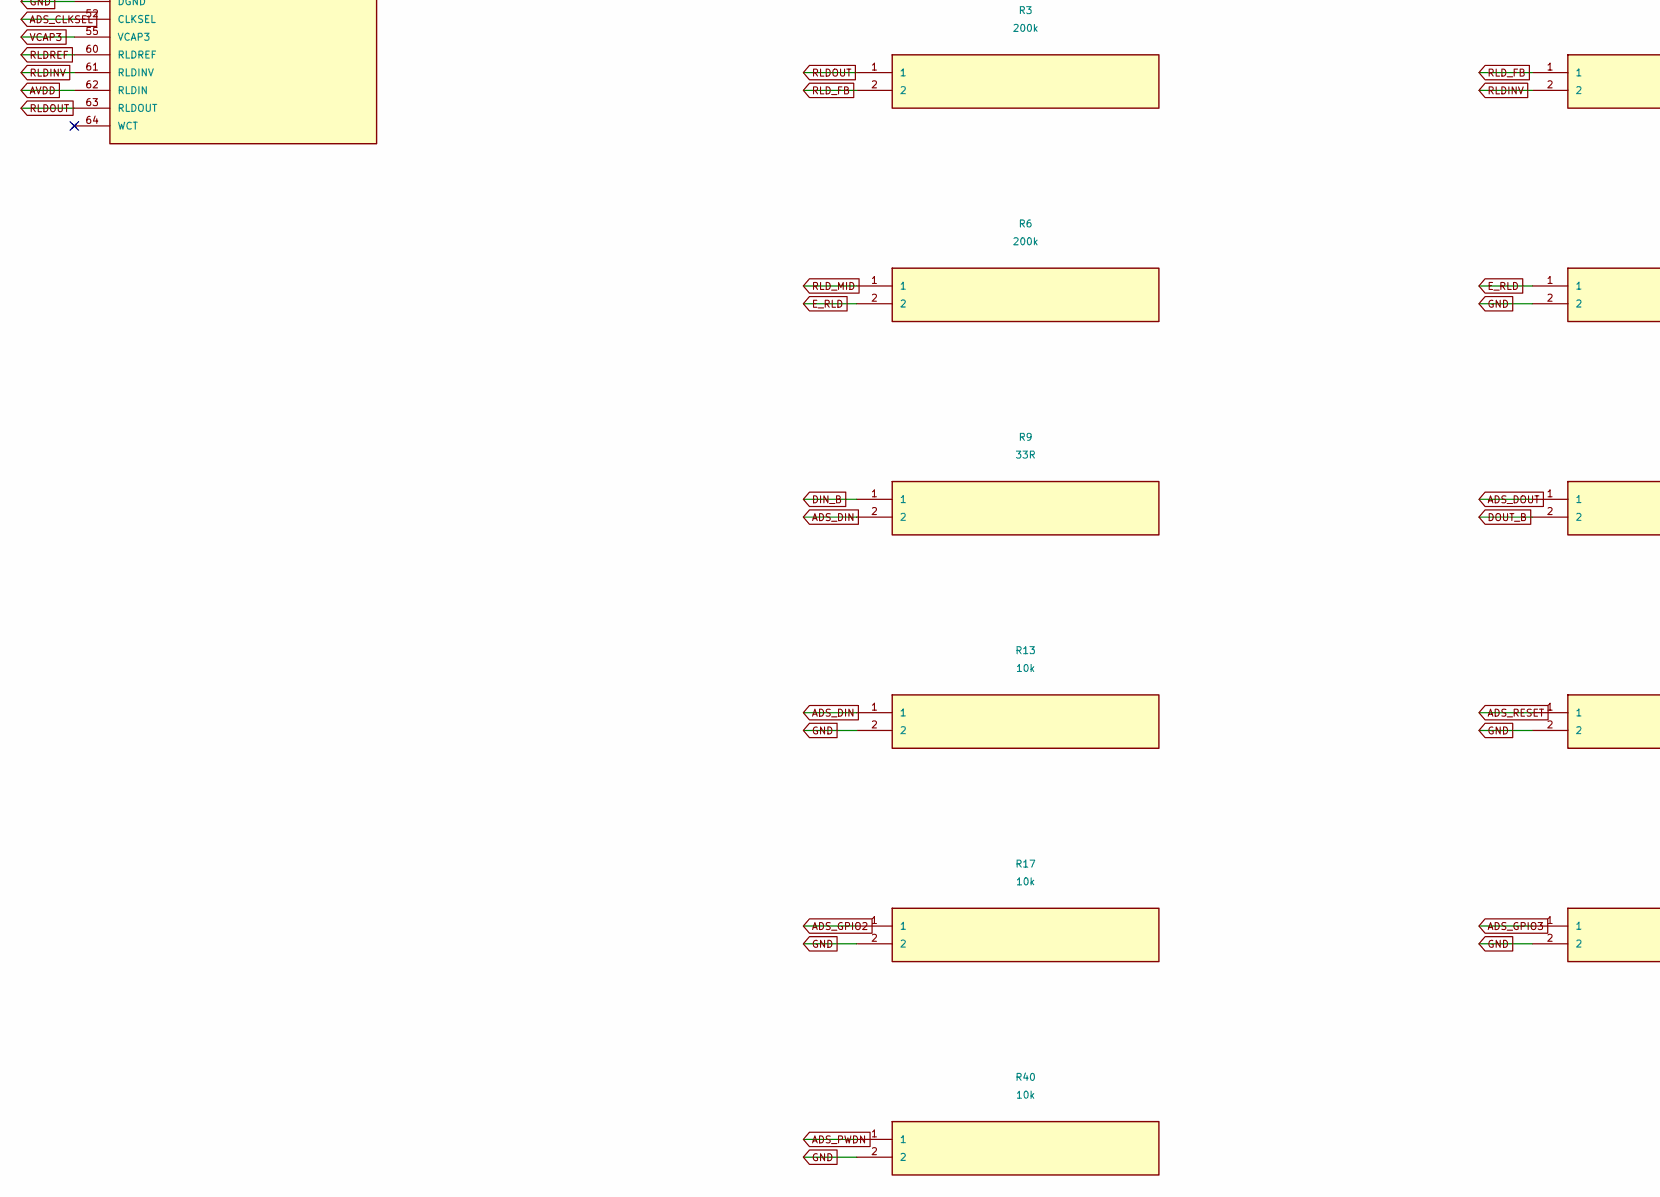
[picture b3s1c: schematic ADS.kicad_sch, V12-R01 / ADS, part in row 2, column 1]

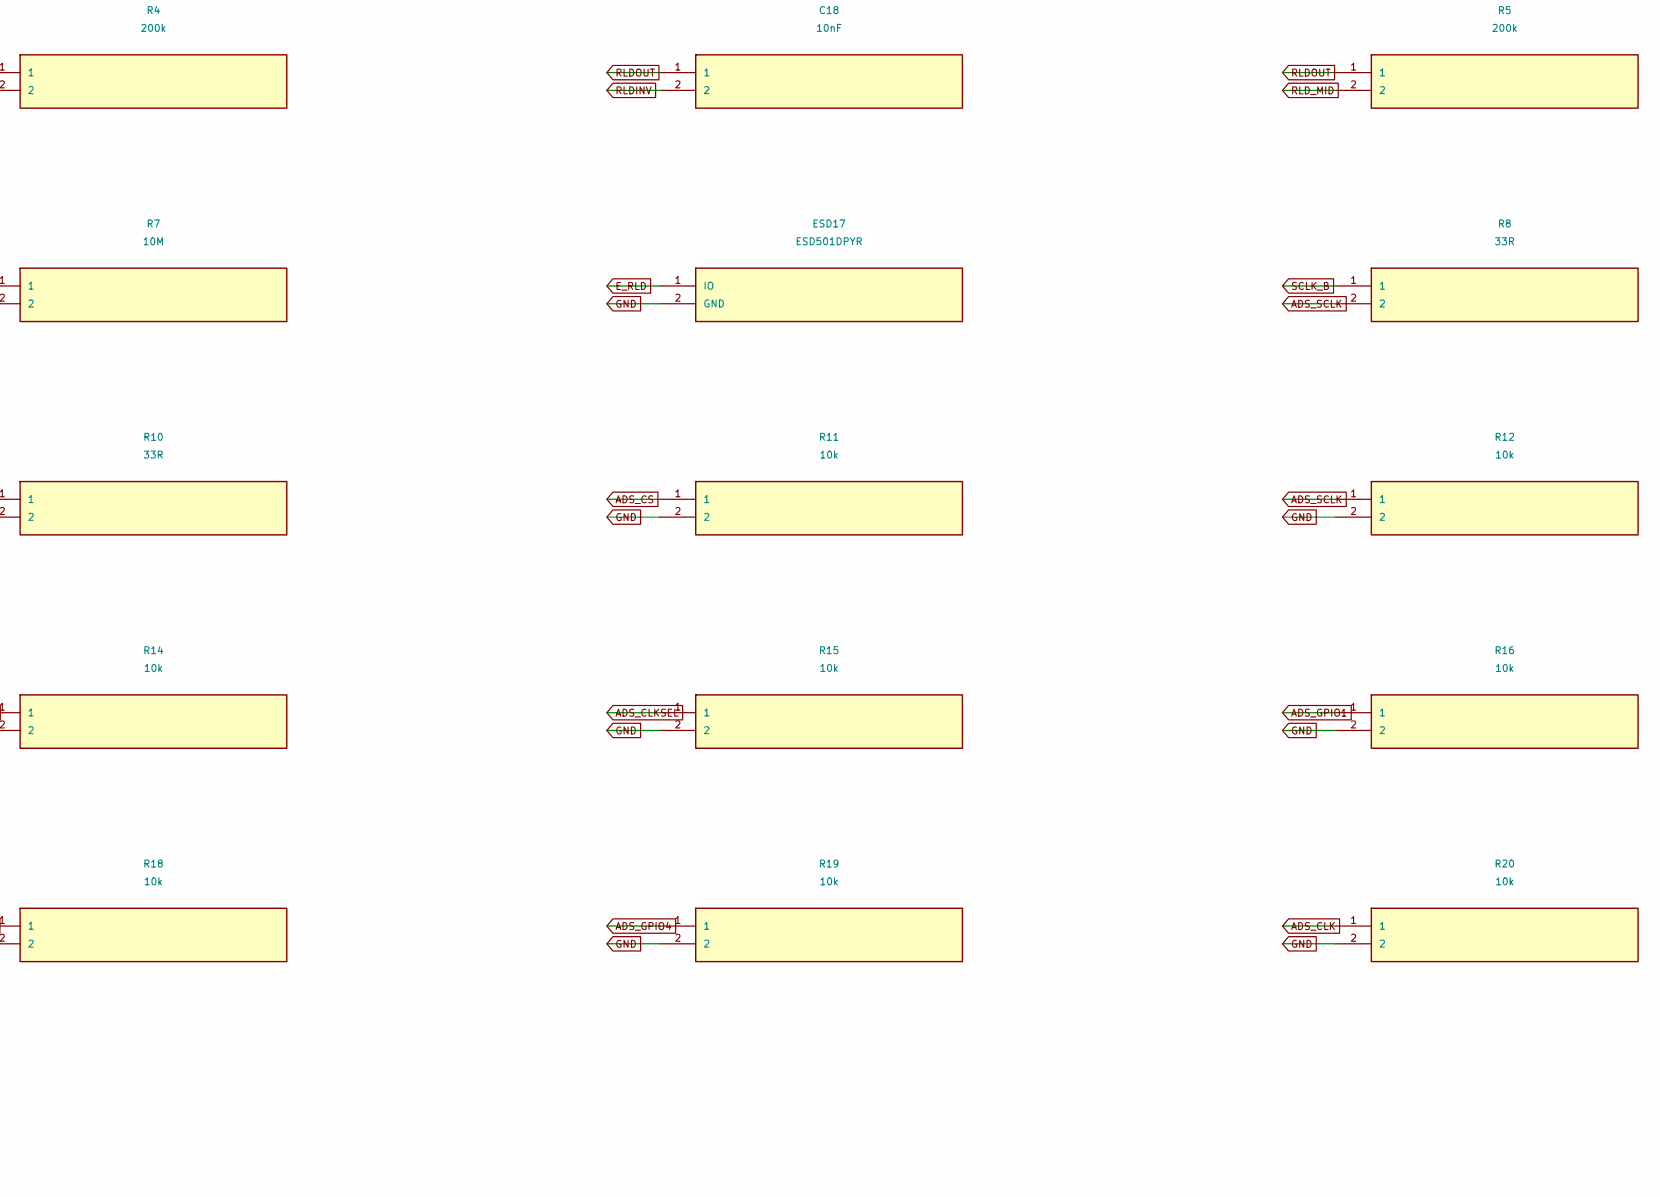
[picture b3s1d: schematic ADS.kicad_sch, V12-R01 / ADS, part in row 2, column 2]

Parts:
C1: 10uF; C_0603_1608Metric
C2, C4, C5, C7, C8, C10, C12, C16, C17: 1uF; C_0402_1005Metric
C3: 22uF; C_0603_1608Metric
C6, C9, C11, C13, C14, C15: 100nF; C_0402_1005Metric
C18: 10nF; C_0402_1005Metric
ESD17: ESD501DPYR; Texas_DPY0002A_0.6x1mm_P0.65mm
R1, R2: 100k; R_0402_1005Metric
R3, R4, R5, R6: 200k; R_0402_1005Metric
R7: 10M; R_0402_1005Metric
R8, R9, R10: 33R; R_0402_1005Metric
R11, R12, R13, R14, R15, R16, R17, R18, R19, R20, R40: 10k; R_0402_1005Metric
U1: ADS1298IPAGR; TQFP-64_10x10mm_P0.5mm

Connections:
ADS_CLK: R20.1, U1.37 (CLK)
ADS_CLKSEL: R15.1, U1.52 (CLKSEL); also elsewhere on the board
ADS_CS: R11.1, U1.39 (CS#); also elsewhere on the board
ADS_DIN: R9.2, R13.1, U1.34 (DIN)
ADS_DOUT: R10.1, U1.43 (DOUT)
ADS_DRDY: U1.47 (DRDY#); also elsewhere on the board
ADS_GPIO1: R16.1, U1.42 (GPIO1)
ADS_GPIO2: R17.1, U1.44 (GPIO2)
ADS_GPIO3: R18.1, U1.45 (GPIO3)
ADS_GPIO4: R19.1, U1.46 (GPIO4)
ADS_IN1N: U1.15 (IN1N); also elsewhere on the board
ADS_IN1P: U1.16 (IN1P); also elsewhere on the board
ADS_IN2N: U1.13 (IN2N); also elsewhere on the board
ADS_IN2P: U1.14 (IN2P); also elsewhere on the board
ADS_IN3N: U1.11 (IN3N); also elsewhere on the board
ADS_IN3P: U1.12 (IN3P); also elsewhere on the board
ADS_IN4N: U1.9 (IN4N); also elsewhere on the board
ADS_IN4P: U1.10 (IN4P); also elsewhere on the board
ADS_IN5N: U1.7 (IN5N); also elsewhere on the board
ADS_IN5P: U1.8 (IN5P); also elsewhere on the board
ADS_IN6N: U1.5 (IN6N); also elsewhere on the board
ADS_IN6P: U1.6 (IN6P); also elsewhere on the board
ADS_IN7N: U1.3 (IN7N); also elsewhere on the board
ADS_IN7P: U1.4 (IN7P); also elsewhere on the board
ADS_IN8N: U1.1 (IN8N); also elsewhere on the board
ADS_IN8P: U1.2 (IN8P); also elsewhere on the board
ADS_PWDN: R40.1, U1.35 (PWDN#); also elsewhere on the board
ADS_RESET: R14.1, U1.36 (RESET#); also elsewhere on the board
ADS_SCLK: R8.2, R12.1, U1.40 (SCLK)
AVDD: C8.1, C9.1, C10.1, C11.1, C12.1, C13.1, R1.1, U1.17 (TESTP_PACE_OUT1), U1.18 (TESTN_PACE_OUT2), U1.19 (AVDD), U1.21 (AVDD), U1.22 (AVDD), U1.54 (AVDD1), U1.56 (AVDD), U1.59 (AVDD), U1.62 (RLDIN); also elsewhere on the board
DIN_B: R9.1; also elsewhere on the board
DOUT_B: R10.2; also elsewhere on the board
DVDD: C14.1, C15.1, C16.1, U1.48 (DVDD), U1.50 (DVDD); also elsewhere on the board
E_RLD: ESD17.1 (IO), R6.2, R7.1; also elsewhere on the board
GND: C1.2, C2.2, C3.2, C4.2, C5.2, C6.2, C7.2, C8.2, C9.2, C10.2, C11.2, C12.2, C13.2, C14.2, C15.2, C16.2, C17.2, ESD17.2 (GND), R2.2, R7.2, R11.2, R12.2, R13.2, R14.2, R15.2, R16.2, R17.2, R18.2, R19.2, R20.2, R40.2, U1.20 (AVSS), U1.23 (AVSS), U1.25 (VREFN), U1.31 (RESV1), U1.32 (AVSS), U1.33 (DGND), U1.38 (START), U1.41 (DAISY_IN), U1.49 (DGND), U1.51 (DGND), U1.53 (AVSS1), U1.57 (AVSS), U1.58 (AVSS); also elsewhere on the board
RLDINV: C18.2, R4.2, U1.61 (RLDINV)
RLDOUT: C18.1, R3.1, R5.1, U1.63 (RLDOUT)
RLDREF: C17.1, R1.2, R2.1, U1.60 (RLDREF)
RLD_FB: R3.2, R4.1
RLD_MID: R5.2, R6.1
SCLK_B: R8.1; also elsewhere on the board
VCAP1: C3.1, U1.28 (VCAP1); also elsewhere on the board
VCAP2: C4.1, U1.30 (VCAP2)
VCAP3: C5.1, C6.1, U1.55 (VCAP3)
VCAP4: C7.1, U1.26 (VCAP4)
VREFP: C1.1, C2.1, U1.24 (VREFP)
